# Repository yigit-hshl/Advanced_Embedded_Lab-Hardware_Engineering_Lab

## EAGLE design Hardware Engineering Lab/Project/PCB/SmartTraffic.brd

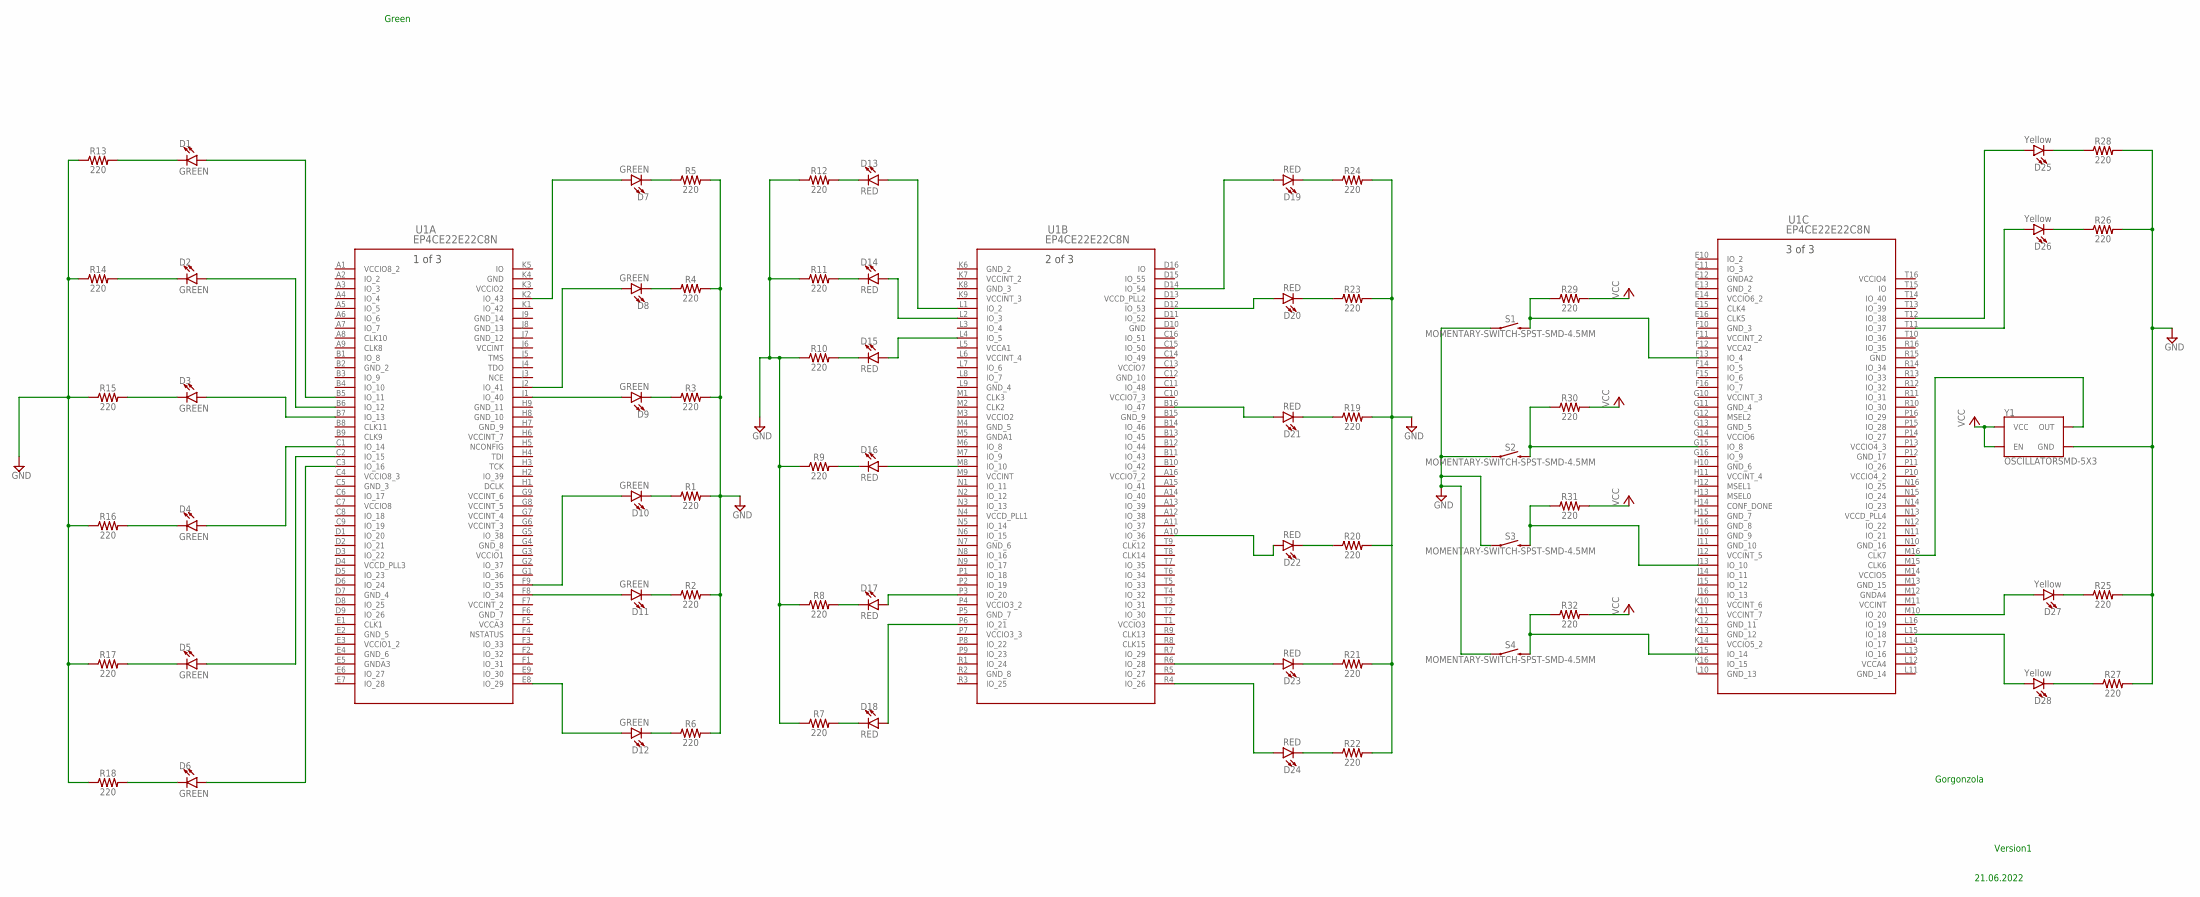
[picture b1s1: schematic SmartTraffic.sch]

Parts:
D1, D2, D3, D4, D5, D6, D7, D8, D9, D10, D11, D12: GREEN; LED-0603
D13, D14, D15, D16, D17, D18, D19, D20, D21, D22, D23, D24: RED; LED-0603
D25, D26, D27, D28: Yellow; LED-0603
R1, R2, R3, R4, R5, R6, R7, R8, R9, R10, R11, R12, R13, R14, R15, R16, R17, R18, R19, R20, R21, R22, R23, R24, R25, R26, R27, R28, R29, R30, R31, R32: 220; 0805
S1, S2, S3, S4: MOMENTARY-SWITCH-SPST-SMD-4.5MM; TACTILE_SWITCH_SMD_4.5MM
U1: EP4CE22E22C8N; FBGA256_THIN_WIRE-BOND-A:1.55_
Y1: OSCILLATORSMD-5X3; OSCILLATOR-SMD-5X3.2

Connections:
GND: R1.2, R2.2, R3.2, R4.2, R5.2, R6.2, R7.1, R8.1, R9.1, R10.1, R11.1, R12.1, R13.1, R14.1, R15.1, R16.1, R17.1, R18.1, R19.2, R20.2, R21.2, R22.2, R23.2, R24.2, R25.2, R26.2, R27.2, R28.2, S1.2 (1), S1.3 (1), S2.2 (1), S2.3 (1), S3.2 (1), S3.3 (1), S4.2 (1), S4.3 (1), Y1.2 (GND)
unnamed: D10.A, U1.F9 (IO_35)
unnamed: D10.C, R1.1
unnamed: D3.A, U1.B7 (IO_13)
unnamed: D3.C, R15.2
unnamed: D4.A, U1.C1 (IO_14)
unnamed: D5.A, U1.C2 (IO_15)
unnamed: D2.A, U1.B6 (IO_12)
unnamed: D1.A, U1.B5 (IO_11)
unnamed: D6.A, U1.C3 (IO_16)
unnamed: D1.C, R13.2
unnamed: D2.C, R14.2
unnamed: D4.C, R16.2
unnamed: D5.C, R17.2
unnamed: D6.C, R18.2
unnamed: D11.A, U1.F8 (IO_34)
unnamed: D12.A, U1.E8 (IO_29)
unnamed: D12.C, R6.1
unnamed: D9.A, U1.J1 (IO_40)
unnamed: D8.A, U1.J2 (IO_41)
unnamed: D11.C, R2.1
unnamed: D9.C, R3.1
unnamed: D8.C, R4.1
unnamed: D7.C, R5.1
unnamed: D7.A, U1.K2 (IO_43)
unnamed: D27.C, R25.1
unnamed: D27.A, U1.M10 (IO_20)
unnamed: D25.A, U1.T12 (IO_38)
unnamed: R29.1, S1.1 (2), S1.4 (2), U1.F13 (IO_4)
unnamed: R30.1, S2.1 (2), S2.4 (2), U1.G15 (IO_8)
unnamed: D16.A, U1.M8 (IO_10)
unnamed: D17.A, U1.P3 (IO_20)
unnamed: D18.A, U1.P6 (IO_21)
unnamed: D15.A, U1.L4 (IO_5)
unnamed: D14.A, U1.L2 (IO_3)
unnamed: D13.A, U1.L1 (IO_2)
unnamed: D13.C, R12.2
unnamed: D14.C, R11.2
unnamed: D15.C, R10.2
unnamed: D16.C, R9.2
unnamed: D17.C, R8.2
unnamed: D18.C, R7.2
unnamed: R31.1, S3.1 (2), S3.4 (2), U1.J13 (IO_10)
unnamed: R32.1, S4.1 (2), S4.4 (2), U1.K15 (IO_14)
unnamed: D26.A, U1.T11 (IO_37)
unnamed: D24.A, U1.R4 (IO_26)
unnamed: D23.A, U1.R6 (IO_28)
unnamed: D22.A, U1.A10 (IO_36)
unnamed: D21.A, U1.B16 (IO_47)
unnamed: D20.A, U1.D12 (IO_53)
unnamed: D19.A, U1.D14 (IO_54)
unnamed: D22.C, R20.1
unnamed: D23.C, R21.1
unnamed: D24.C, R22.1
unnamed: D21.C, R19.1
unnamed: D20.C, R23.1
unnamed: D26.C, R26.1
unnamed: D19.C, R24.1
unnamed: U1.M16 (CLK7), Y1.3 (OUT)
unnamed: D28.A, U1.L15 (IO_18)
unnamed: D28.C, R27.1
unnamed: D25.C, R28.1
VCC: R29.2, R30.2, R31.2, R32.2, Y1.1 (EN), Y1.4 (VCC)
VCCA1: U1.L5 (VCCA1)
VCCA2: U1.F12 (VCCA2)
VCCA3: U1.F5 (VCCA3)
VCCA4: U1.L12 (VCCA4)
VCCD_PLL1: U1.N4 (VCCD_PLL1)
VCCD_PLL2: U1.D13 (VCCD_PLL2)
VCCD_PLL3: U1.D4 (VCCD_PLL3)
VCCD_PLL4: U1.N13 (VCCD_PLL4)
VCCINT: U1.J6 (VCCINT), U1.M9 (VCCINT), U1.M11 (VCCINT)
VCCINT_2: U1.F7 (VCCINT_2), U1.F11 (VCCINT_2), U1.K7 (VCCINT_2)
VCCINT_3: U1.G6 (VCCINT_3), U1.G10 (VCCINT_3), U1.K9 (VCCINT_3)
VCCINT_4: U1.G7 (VCCINT_4), U1.H11 (VCCINT_4), U1.L6 (VCCINT_4)
VCCINT_5: U1.G8 (VCCINT_5), U1.J12 (VCCINT_5)
VCCINT_6: U1.G9 (VCCINT_6), U1.K10 (VCCINT_6)
VCCINT_7: U1.H6 (VCCINT_7), U1.K11 (VCCINT_7)
VCCIO1: U1.G3 (VCCIO1)
VCCIO1_2: U1.E3 (VCCIO1_2)
VCCIO2: U1.K3 (VCCIO2), U1.M3 (VCCIO2)
VCCIO3: U1.T1 (VCCIO3)
VCCIO3_2: U1.P4 (VCCIO3_2)
VCCIO3_3: U1.P7 (VCCIO3_3)
VCCIO4: U1.T16 (VCCIO4)
VCCIO4_2: U1.P10 (VCCIO4_2)
VCCIO4_3: U1.P13 (VCCIO4_3)
VCCIO5: U1.M14 (VCCIO5)
VCCIO5_2: U1.K14 (VCCIO5_2)
VCCIO6: U1.G14 (VCCIO6)
VCCIO6_2: U1.E14 (VCCIO6_2)
VCCIO7: U1.C13 (VCCIO7)
VCCIO7_2: U1.A16 (VCCIO7_2)
VCCIO7_3: U1.C10 (VCCIO7_3)
VCCIO8: U1.C7 (VCCIO8)
VCCIO8_2: U1.A1 (VCCIO8_2)
VCCIO8_3: U1.C4 (VCCIO8_3)

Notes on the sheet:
Green
Version1
21.06.2022
Gorgonzola

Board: 2 copper layers, 66 parts (0 on the bottom side), 71 nets, no tracks yet.

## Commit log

2022-06-13 Add files via upload
    version_2 including servo
2022-06-22 Add files via upload
    All PCB related files for the project
2022-06-22 All PCB related files for project
2022-06-23 All FPGA related work
2022-06-23 UCF file containing 90% of the pins mapping
2022-06-24 Final Documentation.
    All source files and supportive files are included in the PROJECT folder.
2022-06-24 Final Documentation
2022-06-24 Arduino-ESP32 -- AWS-Broker
2022-06-28 Final Presentation
2022-06-29 LabWork_Project_Demonstration
2022-07-06 Format-PPT_PDF
2022-07-06 PCB_Eagle_Schematic_exercise
2022-07-06 PCB_schematic_1bit_fulladder
2022-07-06 PCB_Exercises
2022-07-06 Create 4bit_bcd_adder
2022-07-06 Rename 4bit_bcd_adder to 4bit_bcd_adder.vhd
2022-07-06 Rename d_ff_behavior.vhd.bak to d_ff_behavior_tb.vhd.bak

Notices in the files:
parts and their libraries:
untitled: COPYRIGHT: Copyright (C) 2022 Ultra Librarian. All rights reserved.
SparkFun-LED: Licensing: Creative Commons ShareAlike 4.0 International - https://creativecommons.org/licenses/by-sa/4.0
